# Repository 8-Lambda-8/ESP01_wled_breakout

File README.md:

# ESP01_wled_breakout
ESP01_wled_breakout

ibom:
https://htmlpreview.github.io/?https://raw.githubusercontent.com/8-Lambda-8/ESP01_wled_breakout/main/bom/ibom.html

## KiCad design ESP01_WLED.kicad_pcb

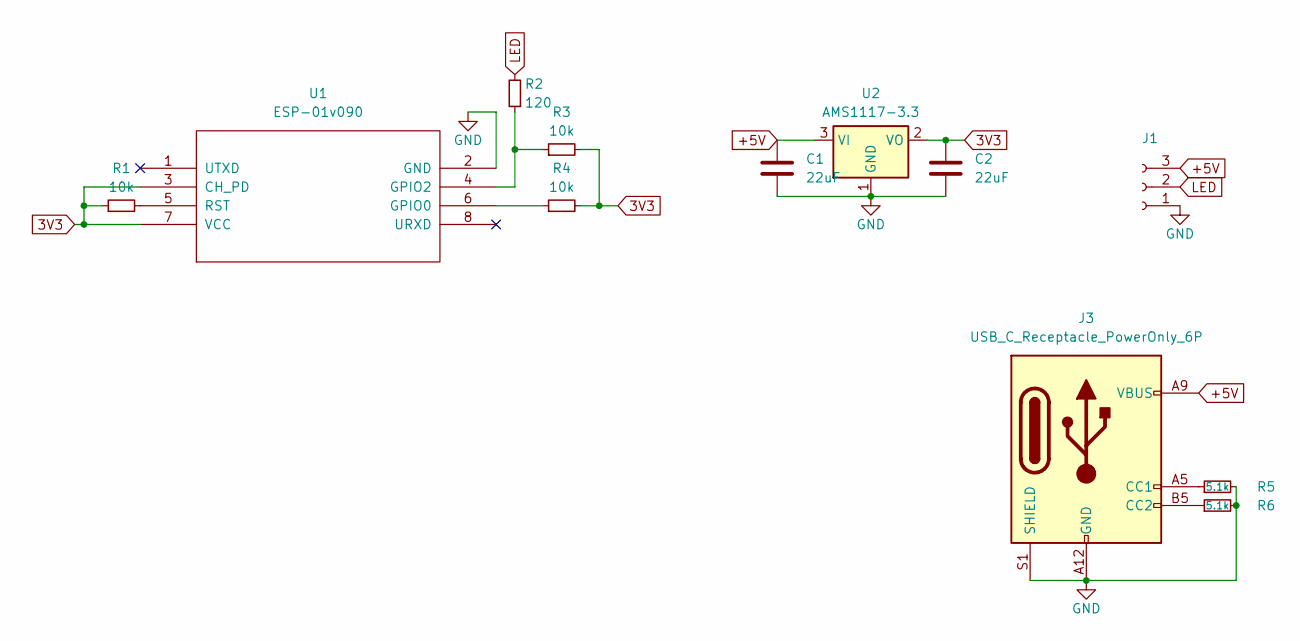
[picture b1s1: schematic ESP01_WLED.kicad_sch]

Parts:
C1, C2: 22uF; C_0805_2012Metric_Pad1.18x1.45mm_HandSolder
J1: PinSocket_1x03_P2.54mm_Horizontal
J3: USB_C_Receptacle_PowerOnly_6P; USB_C_Receptacle_GCT_USB4125-xx-x_6P_TopMnt_Horizontal
R1, R3, R4: 10k; R_0805_2012Metric_Pad1.20x1.40mm_HandSolder
R2: 120; R_0805_2012Metric_Pad1.20x1.40mm_HandSolder
R5, R6: 5.1k; R_0805_2012Metric_Pad1.20x1.40mm_HandSolder
U1: ESP-01v090; ESP-01
U2: AMS1117-3.3; SOT-223-3_TabPin2

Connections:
3V3: C2.1, R1.1, R3.2, R4.2, U1.3 (CH_PD), U1.7 (VCC), U2.2 (VO); also elsewhere on the board
+5V: C1.1, J1.3, J3.A9 (VBUS), J3.B9 (VBUS), U2.3 (VI)
GND: C1.2, C2.2, J1.1, J3.A12 (GND), J3.B12 (GND), J3.S1 (SHIELD), R5.2, R6.2, U1.2 (GND), U2.1 (GND); also elsewhere on the board
LED: J1.2, R2.2
unnamed: J3.A5 (CC1), R5.1
unnamed: J3.B5 (CC2), R6.1
unnamed 6: R4.1, U1.6 (GPIO0); also elsewhere on the board
unnamed 7: R2.1, R3.1, U1.4 (GPIO2); also elsewhere on the board
unnamed 8: R1.2, U1.5 (RST); also elsewhere on the board

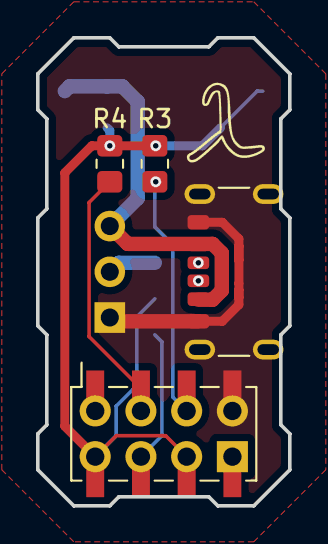
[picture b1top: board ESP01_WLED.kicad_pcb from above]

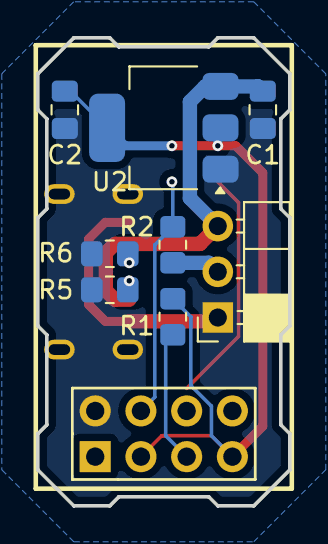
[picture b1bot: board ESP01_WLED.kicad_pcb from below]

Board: 2 copper layers, 14.0 x 26.0 mm, 13 parts (9 on the bottom side), 9 nets.

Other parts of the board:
U1_: PinSocket_2x04_P2.54mm_Vertical_SMD

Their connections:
3V3: U1_.2, U1_.6; also elsewhere on the board
GND: U1_.7; also elsewhere on the board
unnamed 6: U1_.3; also elsewhere on the board
unnamed 7: U1_.5; also elsewhere on the board
unnamed 8: U1_.4; also elsewhere on the board

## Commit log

2025-03-08 init
2025-03-08 added ibom
2025-03-08 usb c
2025-03-08 added ibom link to README.md
2025-03-09 fixed pin socket overlap
